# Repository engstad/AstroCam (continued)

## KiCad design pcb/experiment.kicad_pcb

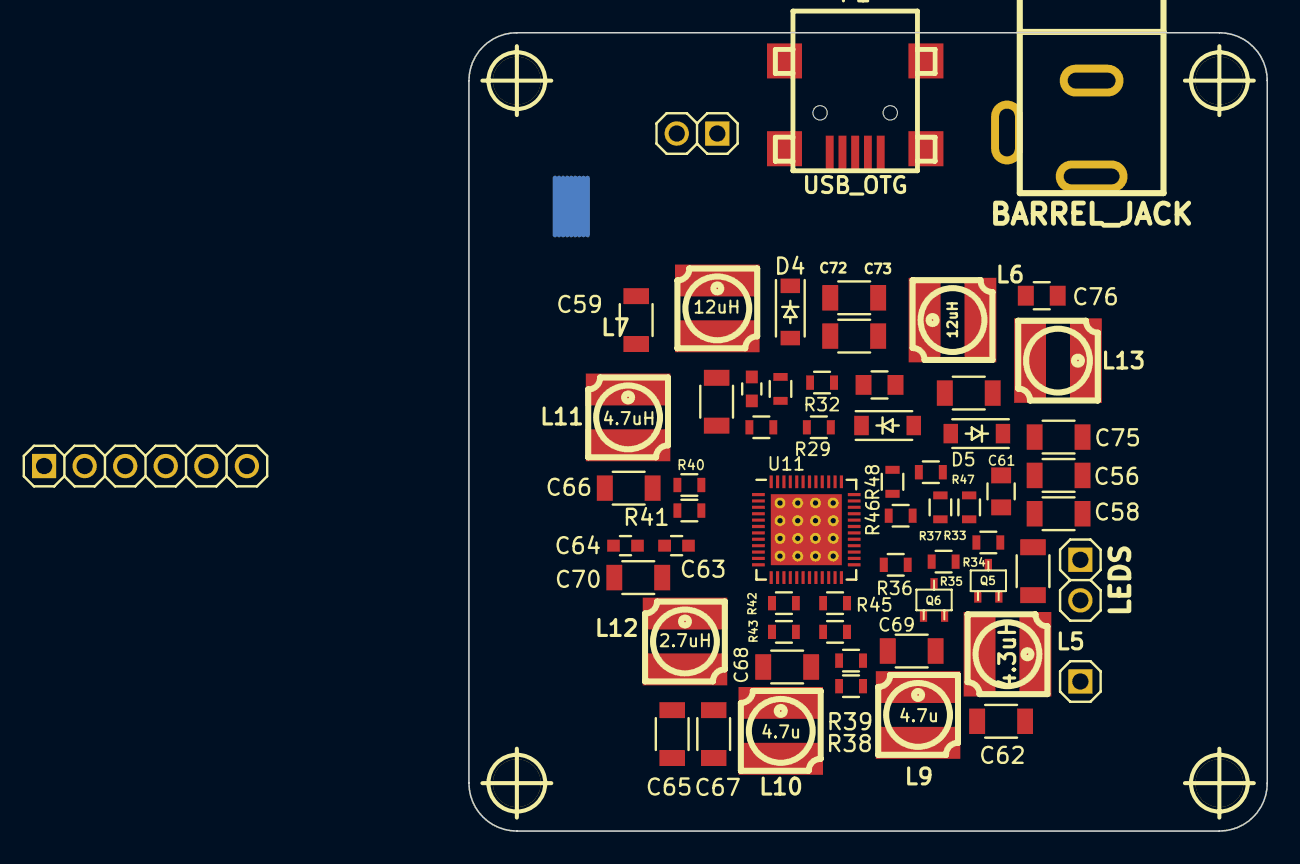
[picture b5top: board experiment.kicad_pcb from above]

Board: 2 copper layers, 50.0 x 50.0 mm, 67 parts (1 on the bottom side), 42 nets, no tracks yet.

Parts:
C55, C56, C58, C72, C75: 10uF; C_1206
C57: 1.0u; C_0603
C59: 10u; C_1206
C60: 3.3uF; C_0805
C61: 4.7u; C_0805
C62, C65: 10.0u; C_1206
C63, C64: 0.1u; C_0603
C66, C67: 47.0u; C_1206
C68, C69, C70, C71: 22u; C_1206
C73, C74: 22uF; C_1206
C76: 10uF; C_0805
CON1: BARREL_JACK; dc_socket
D3, D5: 30V/0.5A; SOD-123
D4: 30V/.5A; SOD-123
L5: 4.3uH; inductor_smd_4.8x2.8mm
L6, L7, L13: 12uH; inductor_smd_4.8x2.8mm
L9, L10: 4.7u; inductor_smd_4.8x2.8mm
L11: 4.7uH; inductor_smd_4.8x2.8mm
L12: 2.7uH; inductor_smd_4.8x2.8mm
P1: USB_OTG; conn_usb_B_mini_smd
P13: CONN_01X06; HDR_1x6
P14: LEDS; HDR_1x2
P15: ADJ; HDR_1x1
P16: CONN_01X02; HDR_1x2
Q5: VEC2611; sc70
Q6: VEC2607; sc70
R29: 11.0k; R_0603
R30, R40, R42: 5.6k; R_0603
R31, R32, R37, R39, R41, R43, R44, R45, R48: 1.0k; R_0603
R33: 3.0k; R_0603
R34, R35, R36: 0.6k; R_0603
R38: 2.0k; R_0603
R46: 10; R_0603
R47: 5.0k; R_0603
T3: NET-TIE; NetTie-I_Connected_SMD
U11: TPS65530; UQFN-48-1EP_6x6mm_Pitch0.4mm
hole_3mm, hole_3mm#2, hole_3mm#3, hole_3mm#4: VAL**; hole_3mm

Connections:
/u-ctrl/EN_AFE: C64.2, U11.6, U11.11, U11.46, U11.47
/u-ctrl/VBATT: C68.1, C69.1, C70.1, C71.1, C72.1, C73.1, C74.1, C76.1, CON1.1, L5.1, L13.1, P1.1, U11.7, U11.12, U11.18, U11.23, U11.40, U11.42, U11.48
/u-ctrl/VOUT_AFE_3V3: C66.1, P13.2, R40.1, U11.4
/u-ctrl/VOUT_BACKL_5V: C75.1, D5.1, P14.1, R47.1
/u-ctrl/VOUT_CCD+: C55.1, D3.1, P16.1, R29.2
/u-ctrl/VOUT_CCD-: C59.1, D4.2, P16.2, R31.2
/u-ctrl/VOUT_CORE_1V2: C65.1, L10.2, P13.4, R44.2
/u-ctrl/VOUT_IO_3V3: C67.1, P13.3, R42.1, U11.16
/u-ctrl/VOUT_MEM_1V8: C62.1, L9.2, P13.5, R38.1
/u-ctrl/VOUT_MOTOR_5V: C56.1, C58.1, C61.1, P13.6, Q5.1, R33.2, U11.29
/u-ctrl/V_BADJ: P15.1, U11.32
GND: C55.2, C56.2, C57.2, C58.2, C59.2, C60.2, C61.2, C62.2, C63.1, C64.1, C65.2, C66.2, C67.2, C68.2, C69.2, C70.2, C71.2, C72.2, C73.2, C74.2, C75.2, C76.2, CON1.2, L7.2, P13.1, Q6.3, R32.2, R39.2, R41.1, R43.1, R45.1, R46.2, T3.2, U11.2, U11.14, U11.20, U11.25, U11.37, U11.49
GNDA: P1.5, T3.1, U11.8, U11.10
unnamed: C57.1, R30.1, U11.45
unnamed: C60.1, L6.1, U11.39
unnamed: C63.2, U11.9
unnamed: D3.2, L6.2, U11.38
unnamed: D4.1, L7.1, U11.43
unnamed: D5.2, L13.2, U11.36
unnamed: L5.2, Q5.3, Q6.1, R35.2
unnamed: L9.1, U11.24
unnamed: L10.1, U11.19
unnamed: L11.1, U11.1
unnamed: L11.2, U11.3
unnamed: L12.1, U11.13
unnamed: L12.2, U11.15
unnamed: P14.2, U11.34
unnamed: Q5.2, R34.2
unnamed: Q6.2, R36.2
unnamed: R29.1, R32.1, U11.41
unnamed: R30.2, R31.1, U11.44
unnamed: R33.1, R37.2, U11.30
unnamed: R34.1, U11.28
unnamed: R35.1, U11.27
unnamed: R36.1, U11.26
unnamed: R37.1, R48.1, U11.31
unnamed: R38.2, R39.1, U11.22
unnamed: R40.2, R41.2, U11.5
unnamed: R42.2, R43.2, U11.17
unnamed: R44.1, R45.2, U11.21
unnamed: R46.1, U11.33
unnamed: R47.2, R48.2, U11.35

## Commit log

2015-06-12 re-arrange directory layout
2015-06-12 initial experimentation with size constraints
2015-06-15 More work on schematic
2015-06-17 Work on proto breakout.
2015-06-21 Lot's of back and forward with vendor.
2015-07-03 more work
2015-08-14 lots of work
2015-08-14 Move into pcb folder
2015-08-14 Add readme
2015-08-19 Confirm to Advanced Circuits
2015-08-20 more stuff
2015-08-22 Cleanups
2015-08-26 Adding ADDI4800 to schematics
2015-08-31 ready for ordering
2015-09-16 Latest, greatest.
2015-09-28 More fiddling
2015-10-09 More.
2015-11-09 latest
2015-11-09 Adding verilog output timing
2015-11-09 adding Teensy SPI initialization code
2015-11-28 Adding power support doc
2016-01-05 xula: adding true clock output and add makefiles
2016-01-05 teensy: Make project compile
2016-01-14 Adding in LVDS reading logic from ADC
2016-06-05 work
2016-06-05 latest src
2017-05-08 lastest at home
2020-10-23 Safety checkin.
2020-10-31 A little more work.
2021-06-15 Work on power system and horizontal driver.
2024-01-12 Start up work to revive this project.
